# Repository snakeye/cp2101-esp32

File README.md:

# Universal programmer for ESP8266/ESP32

The repository contains Eagle CAD project for building programming device for ESP8266/ESP32 microcontrollers.

* Support for popular ESP-01 and ESP-12 modules
* Boot/Reset circuitry for automatic flashing
* Separate +3.3V power line

More info in my blog [https://en.ovcharov.me/2020/09/19/universal-esp8266-esp32-programmer/](https://en.ovcharov.me/2020/09/19/universal-esp8266-esp32-programmer/).

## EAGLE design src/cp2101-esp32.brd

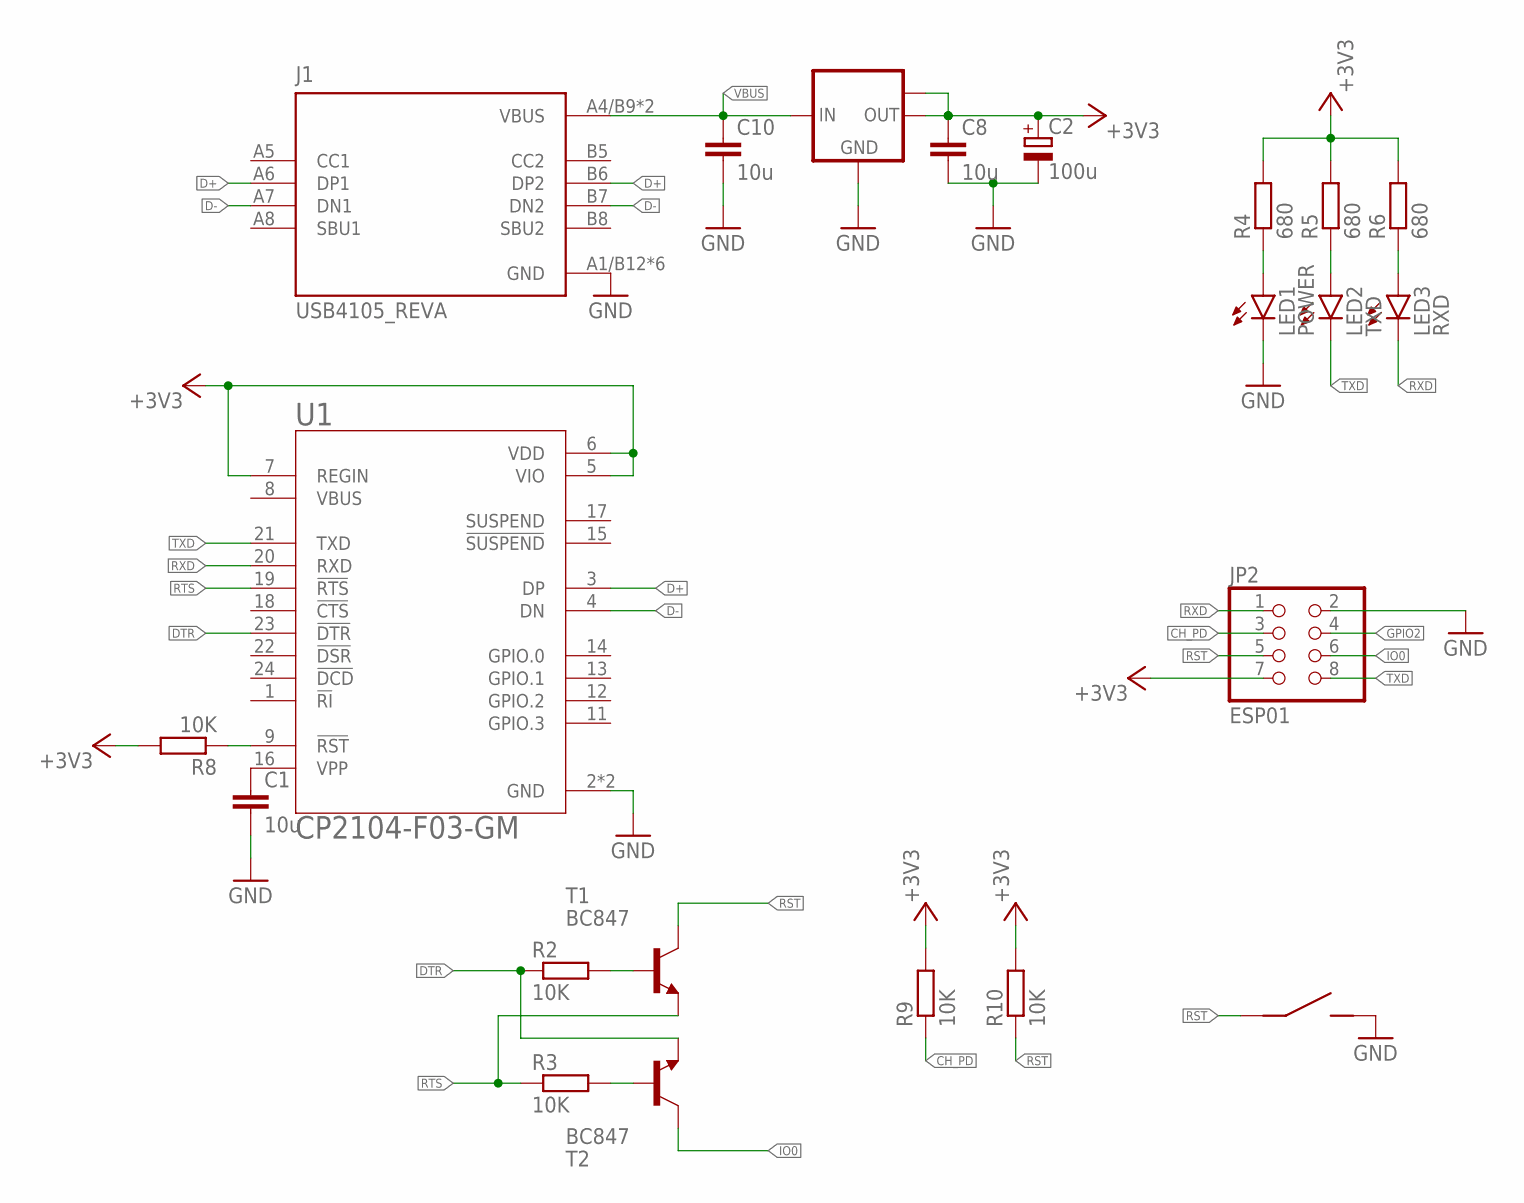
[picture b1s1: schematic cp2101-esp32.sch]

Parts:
C1, C8, C10: 10u; C0805
C2: 100u; A/3216-18R
IC1: LM1117MPX-3.3; SOT223
J1: USB4105_REVA; GCT_USB4105_REVA
JP2: ESP01; 2X04
LED1: POWER; CHIP-LED0805
LED2: TXD; CHIP-LED0805
LED3: RXD; CHIP-LED0805
R2, R3, R8, R9, R10: 10K; R0805
R4, R5, R6: 680; R0805
T1, T2: BC847; SOT23
U1: CP2104-F03-GM; QFN50P400X400X80-25N
U$1: SWITCH2X4-MICRO; 2X4-MICRO

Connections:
+3V3: C2.+, C8.1, IC1.2 (OUT), IC1.TAB (OUT1), JP2.7, R4.2, R5.2, R6.2, R8.2, R9.2, R10.2, U1.5 (VIO), U1.6 (VDD), U1.7 (REGIN)
CH_PD: JP2.3, R9.1
D+: J1.A6 (DP1), J1.B6 (DP2), U1.3 (DP)
D-: J1.A7 (DN1), J1.B7 (DN2), U1.4 (DN)
DTR: R2.1, T2.2 (E), U1.23 (!DTR)
GND: C1.2, C2.-, C8.2, C10.2, IC1.1 (GND), J1.A1/B12 (GND), J1.B1/A12 (GND), J1.G1 (GND), J1.G2 (GND), J1.G3 (GND), J1.G4 (GND), JP2.2, LED1.C, U1.2 (GND), U1.25 (GND), U$1.P$5
GPIO2: JP2.4
IO0: JP2.6, T2.3 (C)
unnamed: R8.1, U1.9 (!RST!)
unnamed: LED1.A, R4.1
unnamed: C1.1, U1.16 (VPP)
unnamed: R2.2, T1.1 (B)
unnamed: R3.2, T2.1 (B)
unnamed: LED2.A, R5.1
unnamed: LED3.A, R6.1
RST: JP2.5, R10.1, T1.3 (C), U$1.P$4
RTS: R3.1, T1.2 (E), U1.19 (!RTS)
RXD: JP2.1, LED3.C, U1.20 (RXD)
TXD: JP2.8, LED2.C, U1.21 (TXD)
VBUS: C10.1, IC1.3 (IN), J1.A4/B9 (VBUS), J1.B4/A9 (VBUS)

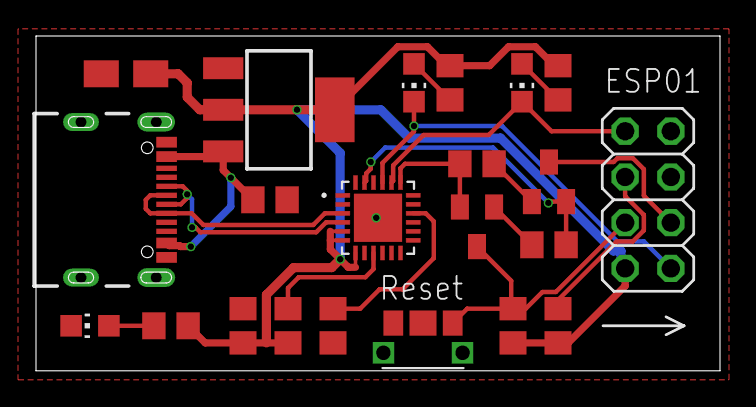
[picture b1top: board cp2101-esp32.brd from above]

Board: 2 copper layers, 38.0 x 18.6 mm, 22 parts (0 on the bottom side), 19 nets.

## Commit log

2020-08-31 Added eagle files
2020-09-01 Added connectors
2020-11-05 USB TypeC connector; Smaller board
